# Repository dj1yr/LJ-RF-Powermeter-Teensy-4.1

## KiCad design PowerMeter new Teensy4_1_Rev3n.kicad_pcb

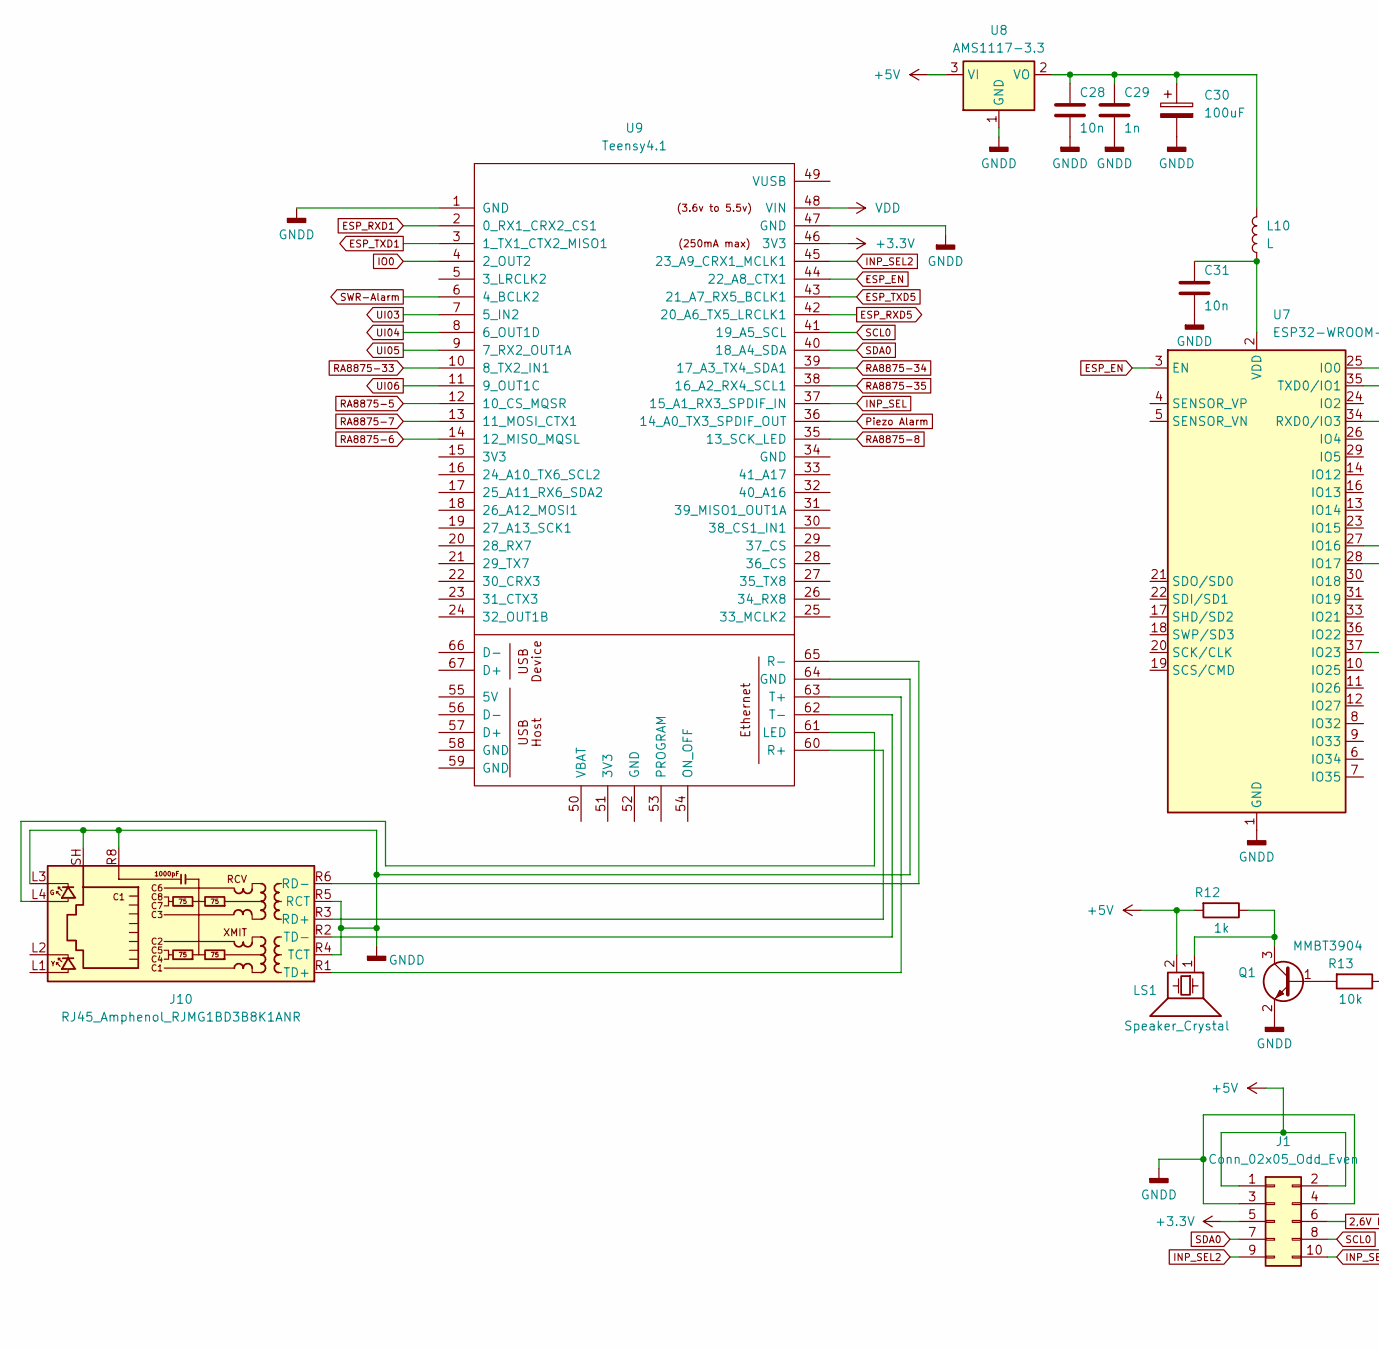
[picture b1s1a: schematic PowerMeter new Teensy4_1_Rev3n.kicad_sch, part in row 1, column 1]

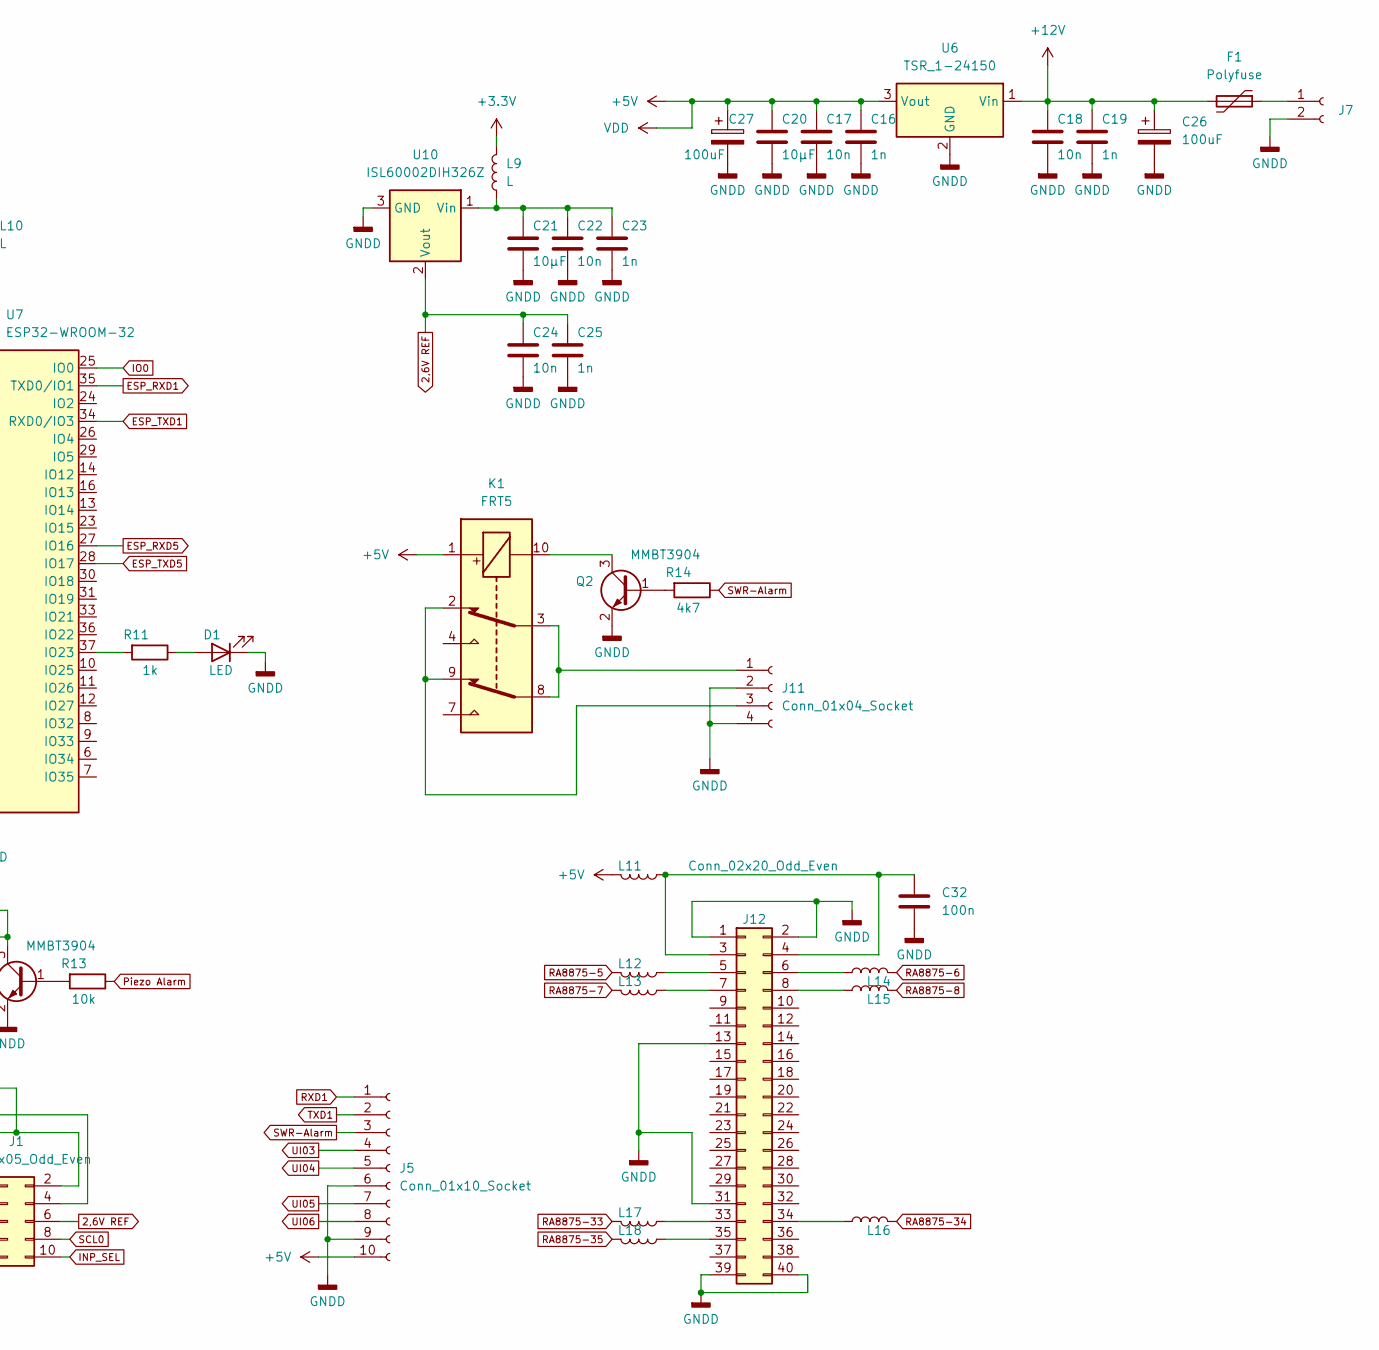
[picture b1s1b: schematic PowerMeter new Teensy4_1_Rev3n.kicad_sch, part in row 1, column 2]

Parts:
C16, C19, C23, C25, C29: 1n; C_1206_3216Metric_Pad1.33x1.80mm_HandSolder
C17, C18, C22, C24, C28, C31: 10n; C_1206_3216Metric_Pad1.33x1.80mm_HandSolder
C20, C21: 10µF; C_1206_3216Metric_Pad1.33x1.80mm_HandSolder
C26, C27, C30: 100uF; CP_Elec_8x11.9
C32: 100n; C_1206_3216Metric_Pad1.33x1.80mm_HandSolder
D1: LED; LED_0805_2012Metric
F1: Polyfuse; Fuse_2512_6332Metric_Pad1.52x3.35mm_HandSolder
J1: Conn_02x05_Odd_Even; PinHeader_2x05_P2.54mm_Vertical
J5: Conn_01x10_Socket; JST_EH_B10B-EH-A_1x10_P2.50mm_Vertical
J7: Conn_01x02_Socket; JST_EH_B2B-EH-A_1x02_P2.50mm_Vertical
J10: RJ45_Amphenol_RJMG1BD3B8K1ANR
J11: Conn_01x04_Socket; JST_EH_B4B-EH-A_1x04_P2.50mm_Vertical
J12: Conn_02x20_Odd_Even; Samtec_HLE-120-02-xx-DV-TE_2x20_P2.54mm_Horizontal
K1: FRT5; Relay_DPDT_FRT5
L9, L10, L11, L12, L13, L14, L15, L16, L17, L18: L; L_1206_3216Metric_Pad1.42x1.75mm_HandSolder
LS1: Speaker_Crystal; Buzzer_TDK_PS1240P02BT_D12.2mm_H6.5mm
Q1, Q2: MMBT3904; SOT-23
R11, R12: 1k; R_0805_2012Metric_Pad1.20x1.40mm_HandSolder
R13: 10k; R_0805_2012Metric_Pad1.20x1.40mm_HandSolder
R14: 4k7; R_0805_2012Metric_Pad1.20x1.40mm_HandSolder
U6: TSR_1-24150; Converter_DCDC_TRACO_TSR-1_THT
U7: ESP32-WROOM-32
U8: AMS1117-3.3; SOT-223-3_TabPin2
U9: Teensy4.1; Teensy41
U10: ISL60002DIH326Z; SOT-23

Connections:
2,6V REF: C24.2, C25.2, J1.6, U10.2 (Vout)
+3.3V: J1.5, L9.2, U9.46 (3V3); also elsewhere on the board
+5V: C16.2, C17.2, C20.2, C27.1, J1.1, J1.2, J5.10, K1.1, L11.2, LS1.2, R12.2, U6.3 (Vout), U8.3 (VI), U9.48 (VIN)
+12V: C18.2, C19.2, C26.1, F1.2, U6.1 (Vin)
ESP_EN: U7.3 (EN), U9.44 (22_A8_CTX1)
ESP_RXD1: U7.35 (TXD0/IO1), U9.2 (0_RX1_CRX2_CS1)
ESP_RXD5: U7.27 (IO16), U9.42 (20_A6_TX5_LRCLK1)
ESP_TXD1: U7.34 (RXD0/IO3), U9.3 (1_TX1_CTX2_MISO1)
ESP_TXD5: U7.28 (IO17), U9.43 (21_A7_RX5_BCLK1)
GNDD: C16.1, C17.1, C18.1, C19.1, C20.1, C21.1, C22.1, C23.1, C24.1, C25.1, C26.2, C27.2, C28.1, C29.1, C30.2, C31.1, C32.1, D1.1 (K), J1.3, J1.4, J5.6, J5.9, J7.2, J10.L3, J10.R4 (TCT), J10.R5 (RCT), J10.R8, J10.SH, J11.2, J11.4, J12.1, J12.2, J12.13, J12.31, J12.39, J12.40, Q1.2 (E), Q2.2 (E), U6.2 (GND), U7.1 (GND), U7.15 (GND), U7.38 (GND), U7.39 (GND), U8.1 (GND), U9.1 (GND), U9.47 (GND), U9.64 (GND), U10.3 (GND)
INP_SEL: J1.10, U9.37 (15_A1_RX3_SPDIF_IN)
INP_SEL2: J1.9, U9.45 (23_A9_CRX1_MCLK1)
IO0: U7.25 (IO0), U9.4 (2_OUT2)
unnamed: D1.2 (A), R11.1
unnamed: F1.1, J7.1
unnamed: J10.R3 (RD+), U9.60 (R+)
unnamed: J10.R6 (RD-), U9.65 (R-)
unnamed: J10.R1 (TD+), U9.63 (T+)
unnamed: J10.R2 (TD-), U9.62 (T-)
unnamed: J11.1, K1.3, K1.8
unnamed: J11.3, K1.2, K1.9
unnamed: C32.2, J12.3, J12.4, L11.1
unnamed: J12.5, L12.1
unnamed: J12.6, L14.1
unnamed: J12.7, L13.1
unnamed: J12.8, L15.1
unnamed: J12.33, L17.1
unnamed: J12.34, L16.1
unnamed: J12.35, L18.1
unnamed: Q1.1 (B), R13.2
unnamed: LS1.1, Q1.3 (C), R12.1
unnamed: Q2.1 (B), R14.2
unnamed: K1.10, Q2.3 (C)
unnamed: R11.2, U7.37 (IO23)
unnamed: C31.2, L10.1, U7.2 (VDD)
unnamed: C28.2, C29.2, C30.1, L10.2, U8.2 (VO)
unnamed: J10.L4, U9.61 (LED)
unnamed: C21.2, C22.2, C23.2, L9.1, U10.1 (Vin)
Piezo Alarm: R13.1, U9.36 (14_A0_TX3_SPDIF_OUT)
RA8875-5: L12.2, U9.12 (10_CS_MQSR)
RA8875-6: L14.2, U9.14 (12_MISO_MQSL)
RA8875-7: L13.2, U9.13 (11_MOSI_CTX1)
RA8875-8: L15.2, U9.35 (13_SCK_LED)
RA8875-33: L17.2, U9.10 (8_TX2_IN1)
RA8875-34: L16.2, U9.39 (17_A3_TX4_SDA1)
RA8875-35: L18.2, U9.38 (16_A2_RX4_SCL1)
RXD1: J5.1
SCL0: J1.8, U9.41 (19_A5_SCL); also elsewhere on the board
SDA0: J1.7, U9.40 (18_A4_SDA); also elsewhere on the board
SWR-Alarm: J5.3, R14.1, U9.6 (4_BCLK2)
TXD1: J5.2
UI03: J5.4, U9.7 (5_IN2)
UI04: J5.5, U9.8 (6_OUT1D)
UI05: J5.7, U9.9 (7_RX2_OUT1A)
UI06: J5.8, U9.11 (9_OUT1C)

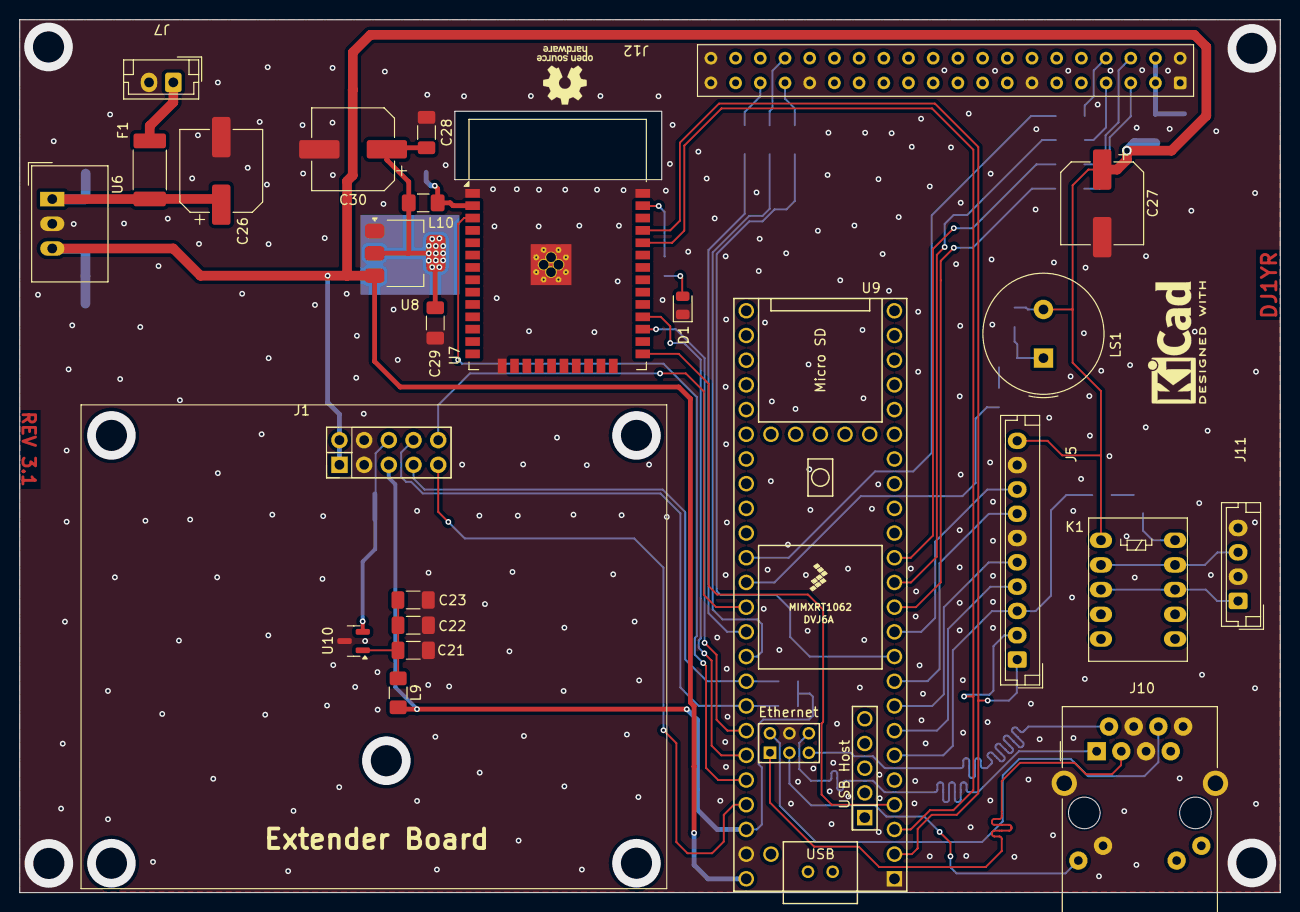
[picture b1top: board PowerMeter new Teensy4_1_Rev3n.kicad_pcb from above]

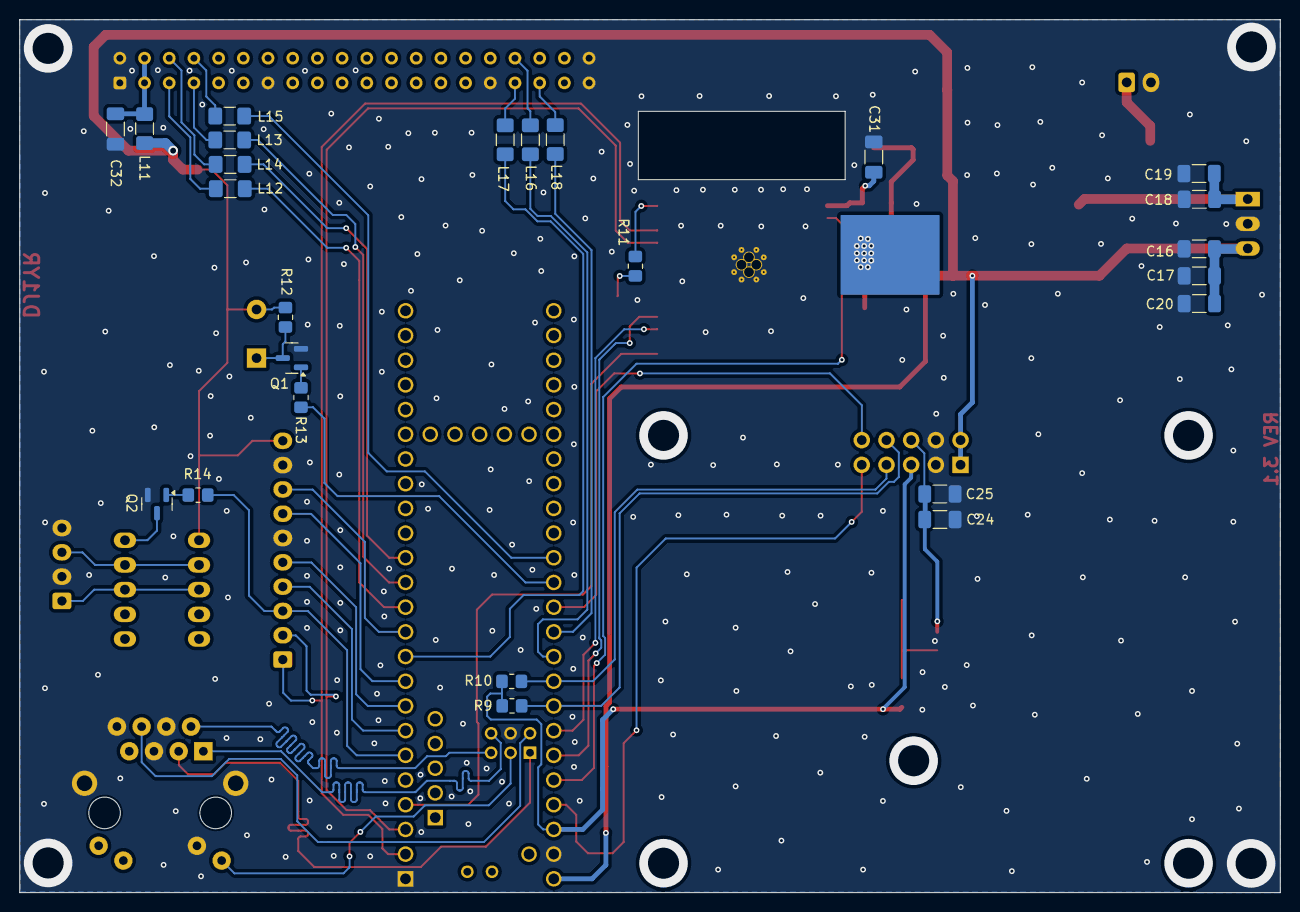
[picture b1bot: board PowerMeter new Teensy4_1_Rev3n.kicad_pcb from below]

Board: 2 copper layers, 129.6 x 89.8 mm, 50 parts (25 on the bottom side), 53 nets.

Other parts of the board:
R9, R10: 2k2; R_0805_2012Metric_Pad1.20x1.40mm_HandSolder

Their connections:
+3.3V: R9.2, R10.2; also elsewhere on the board
SCL0: R9.1; also elsewhere on the board
SDA0: R10.1; also elsewhere on the board

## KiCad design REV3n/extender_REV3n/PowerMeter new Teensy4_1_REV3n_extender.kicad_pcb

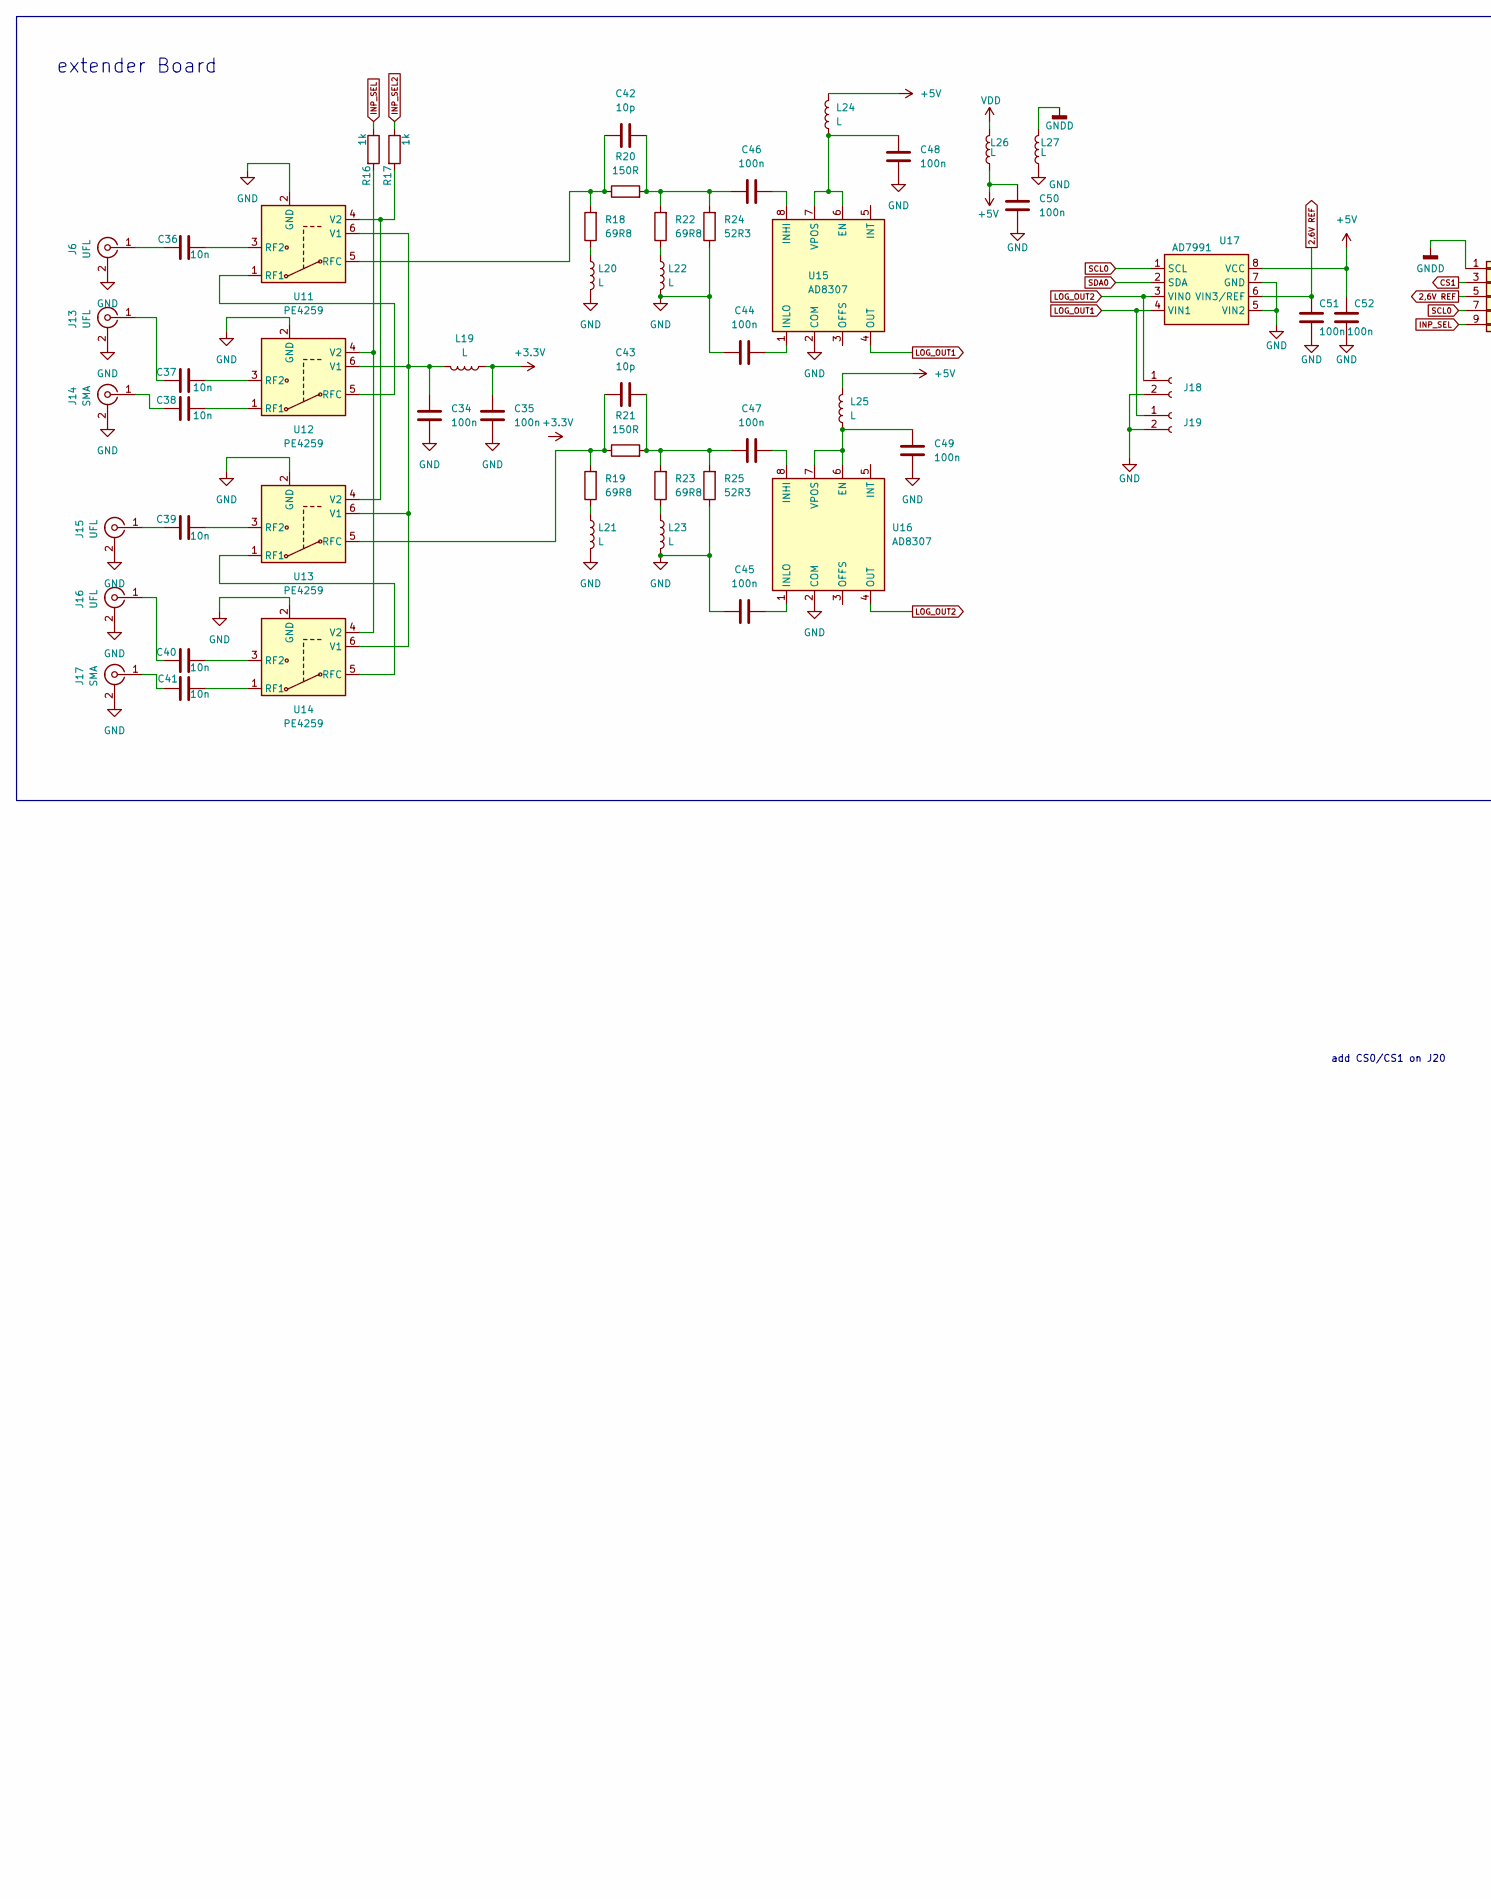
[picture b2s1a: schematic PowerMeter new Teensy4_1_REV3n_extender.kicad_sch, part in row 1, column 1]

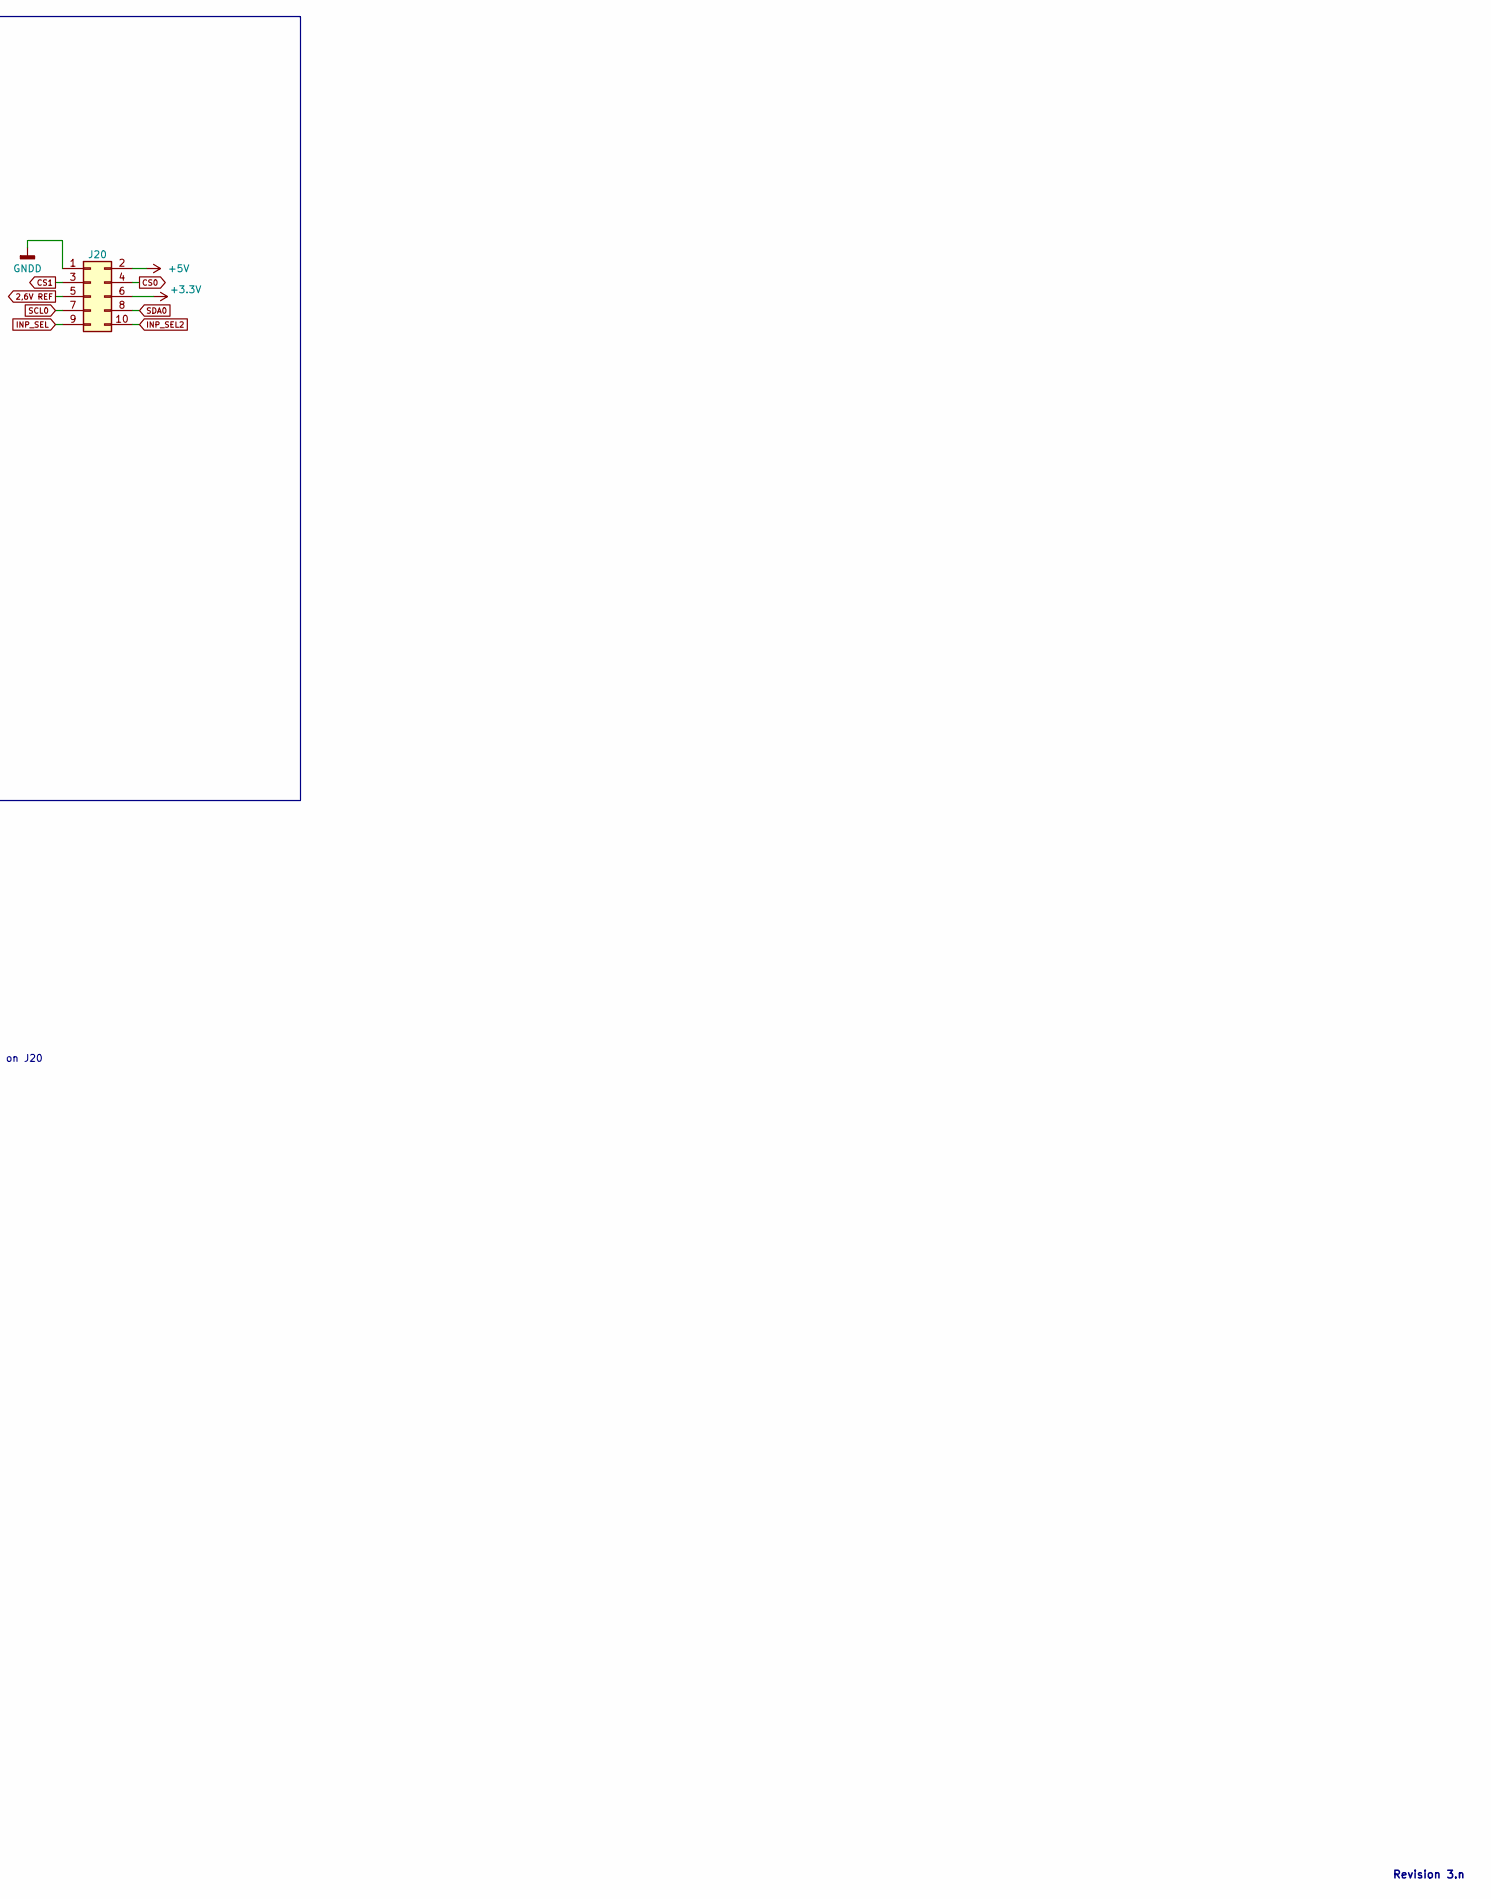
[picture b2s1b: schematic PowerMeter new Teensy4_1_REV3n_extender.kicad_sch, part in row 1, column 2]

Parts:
C34, C35, C44, C45, C46, C47, C48, C49, C50, C51, C52: 100n; C_1206_3216Metric_Pad1.33x1.80mm_HandSolder
C36, C37, C38, C39, C40, C41: 10n; C_1206_3216Metric_Pad1.33x1.80mm_HandSolder
C42, C43: 10p; C_1206_3216Metric_Pad1.33x1.80mm_HandSolder
J6, J13, J15, J16: UFL; U.FL_Molex_MCRF_73412-0110_Vertical
J14, J17: SMA; SMA_BAT_Wireless_BWSMA-KWE-Z001
J18, J19: Conn_01x02_Socket; JST_EH_B2B-EH-A_1x02_P2.50mm_Vertical
J20: Conn_02x05_Odd_Even; PinHeader_2x05_P2.54mm_Vertical
L19, L20, L21, L22, L23, L24, L25, L26, L27: L; L_1206_3216Metric_Pad1.42x1.75mm_HandSolder
R16, R17: 1k; R_0805_2012Metric_Pad1.20x1.40mm_HandSolder
R18, R19, R22, R23: 69R8; R_1206_3216Metric_Pad1.30x1.75mm_HandSolder
R20, R21: 150R; R_1206_3216Metric_Pad1.30x1.75mm_HandSolder
R24, R25: 52R3; R_1206_3216Metric_Pad1.30x1.75mm_HandSolder
U11, U12, U13, U14: PE4259; SOT-363_SC-70-6_Handsoldering
U15, U16: AD8307; SO-8_5.3x6.2mm_P1.27mm
U17: AD7991; TSOT-23-8

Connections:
2,6V REF: C51.2, J20.5, U17.6 (VIN3/REF)
+3.3V: C35.2, J20.6, L19.1
+5V: C50.2, C52.2, J20.2, L24.2, L25.2, L26.1, U17.8 (VCC)
CS0: J20.4
CS1: J20.3
GND: C34.1, C35.1, C44.1, C45.1, C48.1, C49.1, C50.1, C51.1, C52.1, J6.2 (Ext), J13.2 (Ext), J14.2 (Ext), J15.2 (Ext), J16.2 (Ext), J17.2 (Ext), J18.2, J19.2, L20.2, L21.2, L22.2, L23.2, L27.1, R24.1, R25.1, U11.2 (GND), U12.2 (GND), U13.2 (GND), U14.2 (GND), U15.2 (COM), U16.2 (COM), U17.5 (VIN2), U17.7 (GND)
GNDD: J20.1, L27.2
INP_SEL: J20.9, R16.1
INP_SEL2: J20.10, R17.1
LOG_OUT1: J19.1, U15.4 (OUT), U17.4 (VIN1)
LOG_OUT2: J18.1, U16.4 (OUT), U17.3 (VIN0)
unnamed: C42.2, C46.1, R20.2, R22.2, R24.2
unnamed: C43.2, C47.1, R21.2, R23.2, R25.2
unnamed: C36.1, J6.1 (In)
unnamed: C37.1, J13.1 (In)
unnamed: C38.1, J14.1 (In)
unnamed: C39.1, J15.1 (In)
unnamed: C40.1, J16.1 (In)
unnamed: C41.1, J17.1 (In)
unnamed: L20.1, R18.1
unnamed: L21.1, R19.1
unnamed: L22.1, R22.1
unnamed: L23.1, R23.1
unnamed: U11.1 (RF1), U12.5 (RFC)
unnamed: C36.2, U11.3 (RF2)
unnamed: C42.1, R18.2, R20.1, U11.5 (RFC)
unnamed: C34.2, L19.2, U11.6 (V1), U12.6 (V1), U13.6 (V1), U14.6 (V1)
unnamed: R17.2, U11.4 (V2), U13.4 (V2)
unnamed: C38.2, U12.1 (RF1)
unnamed: C37.2, U12.3 (RF2)
unnamed: R16.2, U12.4 (V2), U14.4 (V2)
unnamed: U13.1 (RF1), U14.5 (RFC)
unnamed: C39.2, U13.3 (RF2)
unnamed: C43.1, R19.2, R21.1, U13.5 (RFC)
unnamed: C41.2, U14.1 (RF1)
unnamed: C40.2, U14.3 (RF2)
unnamed: C48.2, L24.1, U15.6 (EN), U15.7 (VPOS)
unnamed: C46.2, U15.8 (INHI)
unnamed: C44.2, U15.1 (INLO)
unnamed: C49.2, L25.1, U16.6 (EN), U16.7 (VPOS)
unnamed: C47.2, U16.8 (INHI)
unnamed: C45.2, U16.1 (INLO)
SCL0: J20.7, U17.1 (SCL)
SDA0: J20.8, U17.2 (SDA)
VDD: L26.2

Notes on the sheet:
add CS0/CS1 on J20
extender Board
Revision 3.n

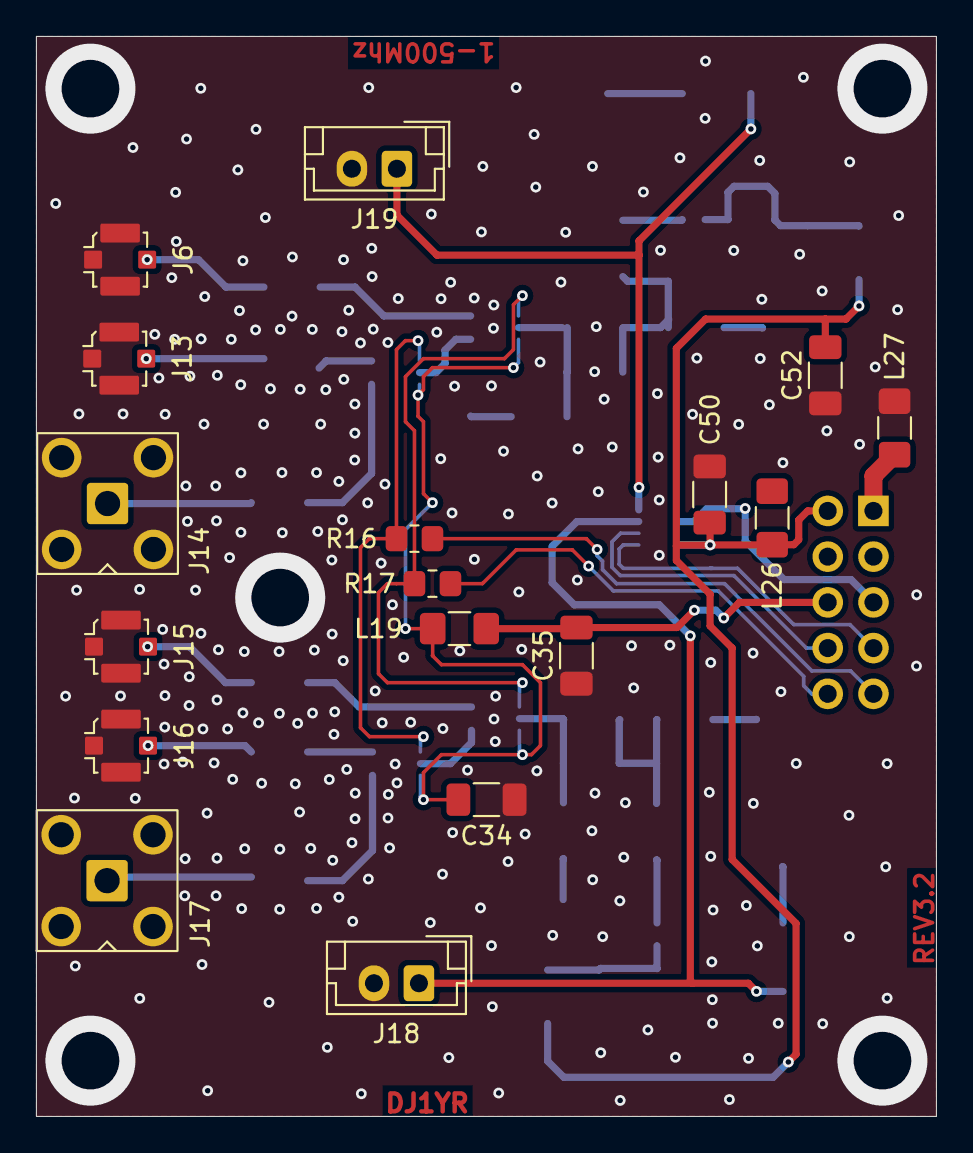
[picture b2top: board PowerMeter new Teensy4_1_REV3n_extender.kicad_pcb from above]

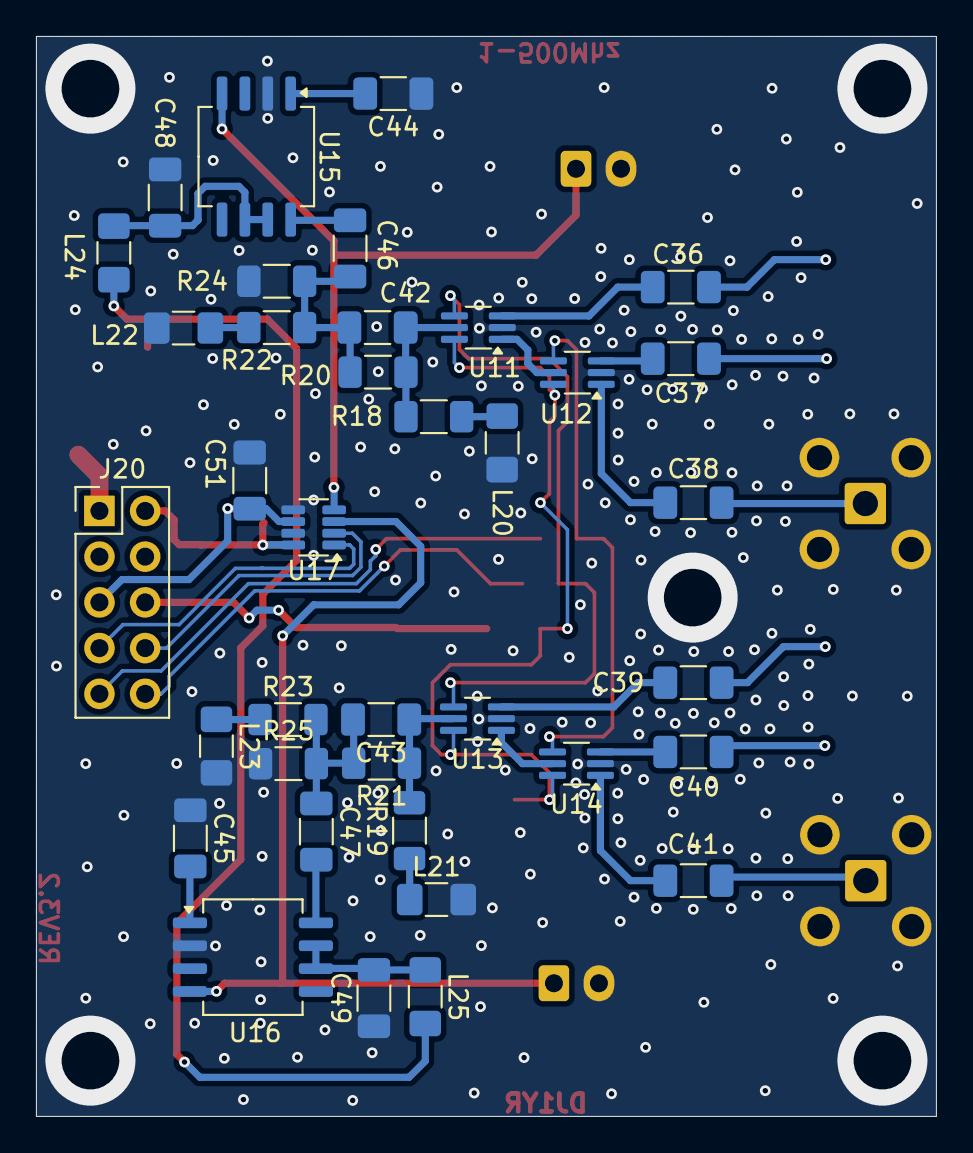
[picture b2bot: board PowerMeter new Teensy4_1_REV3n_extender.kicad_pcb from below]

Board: 2 copper layers, 50.0 x 60.0 mm, 54 parts (37 on the bottom side), 42 nets.
